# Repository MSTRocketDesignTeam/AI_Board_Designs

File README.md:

# AI_Board_Designs
This is the repo for all of the KiCad documentation for any AI Board changes.

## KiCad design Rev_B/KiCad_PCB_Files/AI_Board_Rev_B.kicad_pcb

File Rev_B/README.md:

This is the folder location for Rev_B of the AI Board designed by Isaac Lough for Missouri S&T Rocket Design Team.

The documentaiton for all of the reasoning is located here: https://mailmissouri.sharepoint.com/:w:/r/sites/RocketDesignTeam409-Ogrp/_layouts/15/Doc.aspx?sourcedoc=%7B42161E26-5CDD-4F6A-B8BB-66B7CA16C9B1%7D&file=AI%20Board%20Redesign%20-%20Unofficial%20Preliminary%20Research.docx&action=default&mobileredirect=true

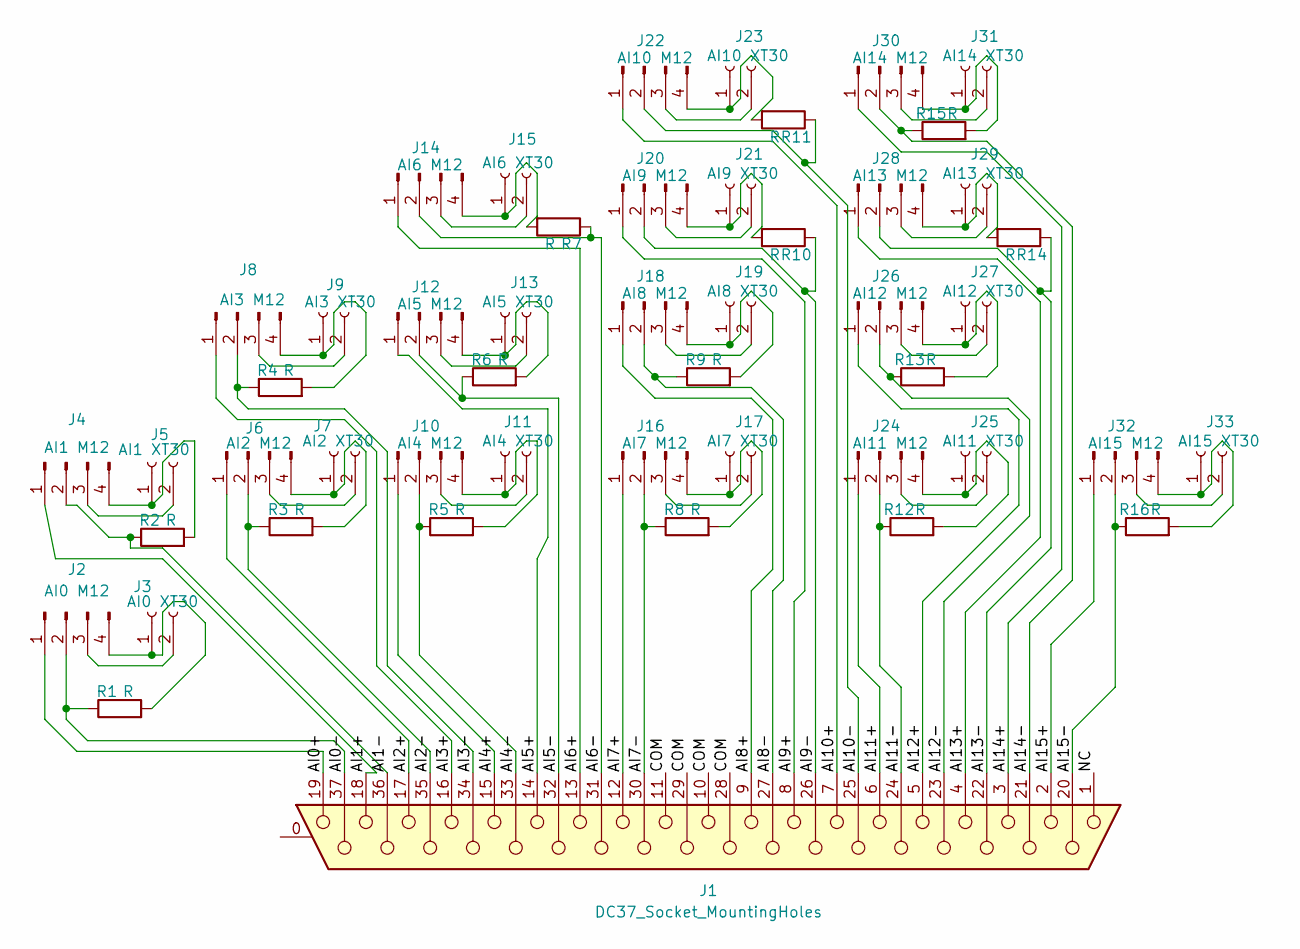
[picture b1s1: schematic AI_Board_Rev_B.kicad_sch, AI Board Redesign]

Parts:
J1: DC37_Socket_MountingHoles; DSUB-37_Socket_Vertical_P2.77x2.84mm_MountingHoles
J2: AI0 M12; M12 A-Code Amphenol
J3: AI0 XT30; AMASS_XT30U-F_1x02_P5.0mm_Vertical
J4: AI1 M12; M12 A-Code Amphenol
J5: AI1 XT30; AMASS_XT30U-F_1x02_P5.0mm_Vertical
J6: AI2 M12; M12 A-Code Amphenol
J7: AI2 XT30; AMASS_XT30U-F_1x02_P5.0mm_Vertical
J8: AI3 M12; M12 A-Code Amphenol
J9: AI3 XT30; AMASS_XT30U-F_1x02_P5.0mm_Vertical
J10: AI4 M12; M12 A-Code Amphenol
J11: AI4 XT30; AMASS_XT30U-F_1x02_P5.0mm_Vertical
J12: AI5 M12; M12 A-Code Amphenol
J13: AI5 XT30; AMASS_XT30U-F_1x02_P5.0mm_Vertical
J14: AI6 M12; M12 A-Code Amphenol
J15: AI6 XT30; AMASS_XT30U-F_1x02_P5.0mm_Vertical
J16: AI7 M12; M12 A-Code Amphenol
J17: AI7 XT30; AMASS_XT30U-F_1x02_P5.0mm_Vertical
J18: AI8 M12; M12 A-Code Amphenol
J19: AI8 XT30; AMASS_XT30U-F_1x02_P5.0mm_Vertical
J20: AI9 M12; M12 A-Code Amphenol
J21: AI9 XT30; AMASS_XT30U-F_1x02_P5.0mm_Vertical
J22: AI10 M12; M12 A-Code Amphenol
J23: AI10 XT30; AMASS_XT30U-F_1x02_P5.0mm_Vertical
J24: AI11 M12; M12 A-Code Amphenol
J25: AI11 XT30; AMASS_XT30U-F_1x02_P5.0mm_Vertical
J26: AI12 M12; M12 A-Code Amphenol
J27: AI12 XT30; AMASS_XT30U-F_1x02_P5.0mm_Vertical
J28: AI13 M12; M12 A-Code Amphenol
J29: AI13 XT30; AMASS_XT30U-F_1x02_P5.0mm_Vertical
J30: AI14 M12; M12 A-Code Amphenol
J31: AI14 XT30; AMASS_XT30U-F_1x02_P5.0mm_Vertical
J32: AI15 M12; M12 A-Code Amphenol
J33: AI15 XT30; AMASS_XT30U-F_1x02_P5.0mm_Vertical
R1, R2, R3, R4, R5, R6, R7, R8, R9, R10, R11, R12, R13, R14, R15, R16: R; R_Axial_DIN0207_L6.3mm_D2.5mm_P10.16mm_Horizontal

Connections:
/AI0+: J1.19, J2.1
/AI0-: J1.37, J2.2, R1.1
/AI1+: J1.18, J4.1
/AI1-: J1.36, J4.2, R2.1
/AI2+: J1.17, J6.1
/AI2-: J1.35, J6.2, R3.1
/AI3+: J1.16, J8.1
/AI3-: J1.34, J8.2, R4.1
/AI4+: J1.15, J10.1
/AI4-: J1.33, J10.2, R5.1
/AI5+: J1.14, J12.1
/AI5-: J1.32, J12.2, R6.1
/AI6+: J1.13, J14.1
/AI6-: J1.31, J14.2, R7.1
/AI7+: J1.12, J16.1
/AI7-: J1.30, J16.2, R8.1
/AI8+: J1.9, J18.1
/AI8-: J1.27, J18.2, R9.1
/AI9+: J1.8, J20.1
/AI9-: J1.26, J20.2, R10.1
/AI10+: J1.7, J22.1
/AI10-: J1.25, J22.2, R11.1
/AI11+: J1.6, J24.1
/AI11-: J1.24, J24.2, R12.1
/AI12+: J1.5, J26.1
/AI12-: J1.23, J26.2, R13.1
/AI13+: J1.4, J28.1
/AI13-: J1.22, J28.2, R14.1
/AI14+: J1.3, J30.1
/AI14-: J1.21, J30.2, R15.1
/AI15+: J1.2, J32.1
/AI15-: J1.20, J32.2, R16.1
/COM: J1.10, J1.11, J1.28, J1.29
/NC: J1.1
unnamed: J2.3, J3.2
unnamed: J2.4, J3.1, R1.2
unnamed: J4.3, J5.2
unnamed: J4.4, J5.1, R2.2
unnamed: J6.3, J7.2
unnamed: J6.4, J7.1, R3.2
unnamed: J8.3, J9.2
unnamed: J8.4, J9.1, R4.2
unnamed: J10.3, J11.2
unnamed: J10.4, J11.1, R5.2
unnamed: J12.3, J13.2
unnamed: J12.4, J13.1, R6.2
unnamed: J14.3, J15.2
unnamed: J14.4, J15.1, R7.2
unnamed: J16.3, J17.2
unnamed: J16.4, J17.1, R8.2
unnamed: J18.3, J19.2
unnamed: J18.4, J19.1, R9.2
unnamed: J20.3, J21.2
unnamed: J20.4, J21.1, R10.2
unnamed: J22.3, J23.2
unnamed: J22.4, J23.1, R11.2
unnamed: J24.3, J25.2
unnamed: J24.4, J25.1, R12.2
unnamed: J26.3, J27.2
unnamed: J26.4, J27.1, R13.2
unnamed: J28.3, J29.2
unnamed: J28.4, J29.1, R14.2
unnamed: J30.3, J31.2
unnamed: J30.4, J31.1, R15.2
unnamed: J32.3, J33.2
unnamed: J32.4, J33.1, R16.2

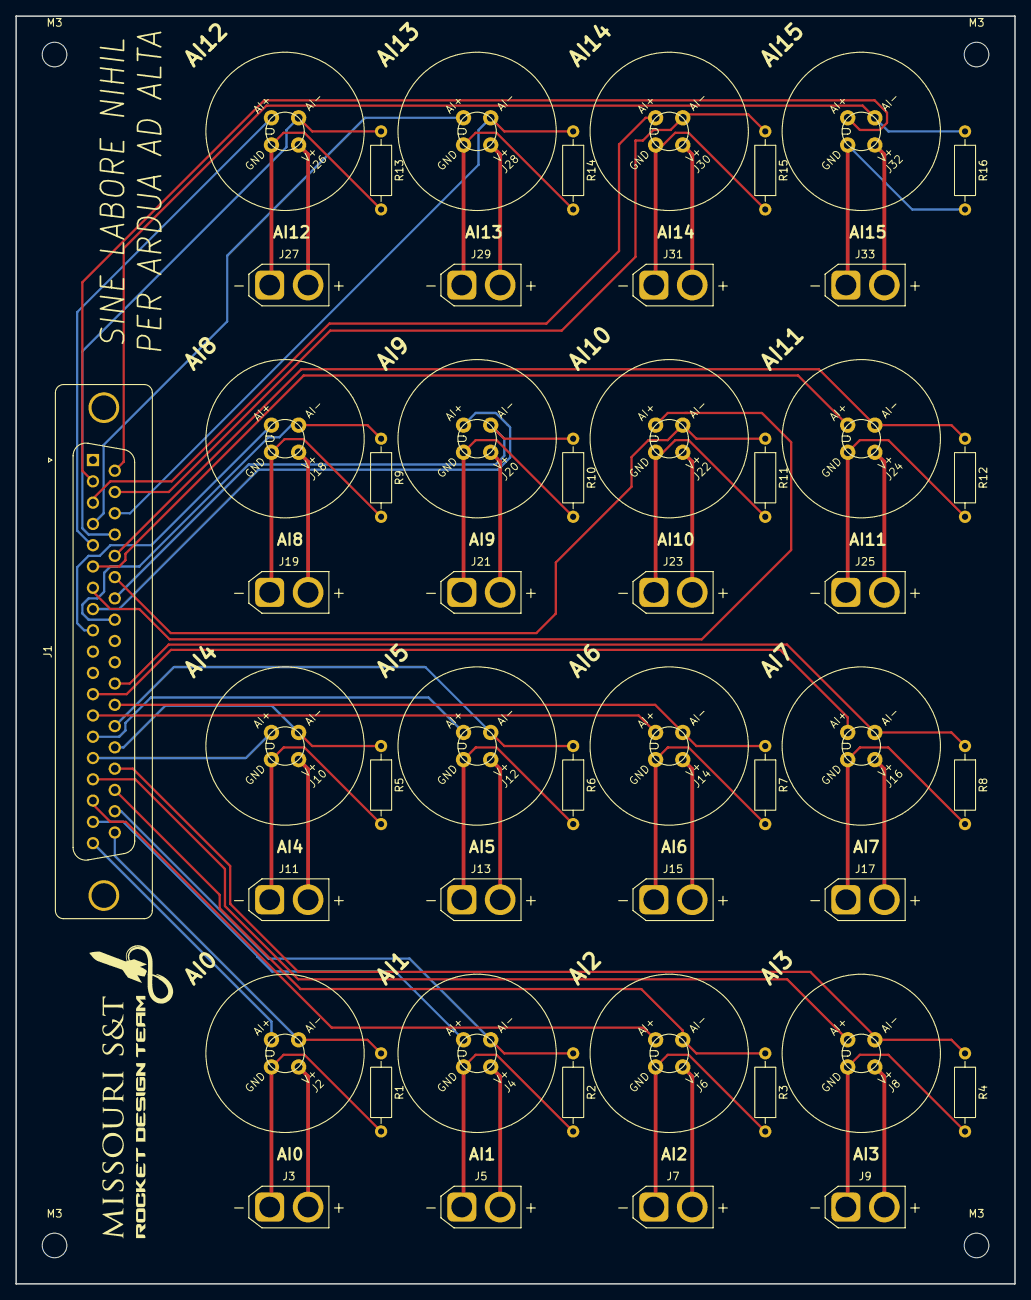
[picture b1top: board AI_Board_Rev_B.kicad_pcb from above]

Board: 2 copper layers, 130.0 x 165.0 mm, 53 parts (0 on the bottom side), 65 nets.

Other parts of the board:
M3, M3#2, M3#3, M3#4: MountingHole_3.2mm_M3

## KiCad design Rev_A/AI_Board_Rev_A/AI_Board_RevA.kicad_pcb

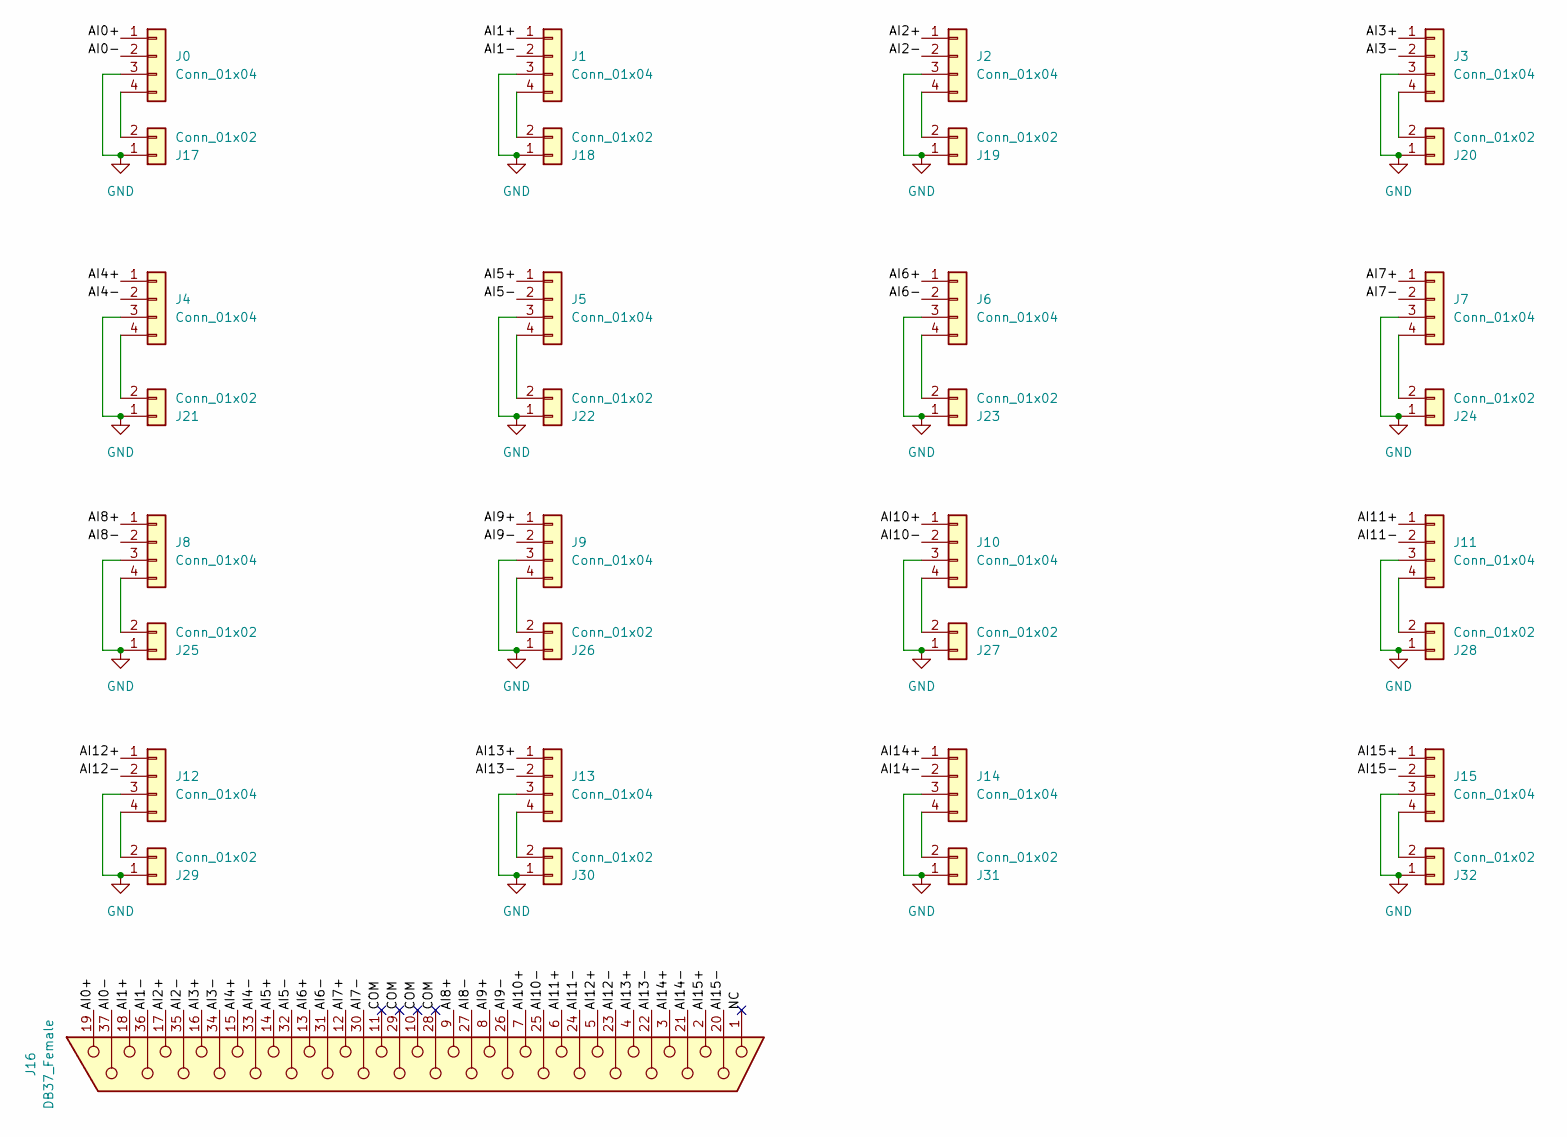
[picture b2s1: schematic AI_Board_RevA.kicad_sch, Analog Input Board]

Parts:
J0, J1, J2, J3, J4, J5, J6, J7, J8, J9, J10, J11, J12, J13, J14, J15: Conn_01x04; TENSILITY_54-00278
J16: DB37_Female; DSUB-37_Female_Vertical_P2.77x2.84mm_MountingHoles
J17, J18, J19, J20, J21, J22, J23, J24, J25, J26, J27, J28, J29, J30, J31, J32: Conn_01x02; AMASS_XT30UPB-F_1x02_P5.0mm_Vertical

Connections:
/AI0+: J0.1, J16.19
/AI0-: J0.2, J16.37
/AI1+: J1.1, J16.18
/AI1-: J1.2, J16.36
/AI2+: J2.1, J16.17
/AI2-: J2.2, J16.35
/AI3+: J3.1, J16.16
/AI3-: J3.2, J16.34
/AI4+: J4.1, J16.15
/AI4-: J4.2, J16.33
/AI5+: J5.1, J16.14
/AI5-: J5.2, J16.32
/AI6+: J6.1, J16.13
/AI6-: J6.2, J16.31
/AI7+: J7.1, J16.12
/AI7-: J7.2, J16.30
/AI8+: J8.1, J16.9
/AI8-: J8.2, J16.27
/AI9+: J9.1, J16.8
/AI9-: J9.2, J16.26
/AI10+: J10.1, J16.7
/AI10-: J10.2, J16.25
/AI11+: J11.1, J16.6
/AI11-: J11.2, J16.24
/AI12+: J12.1, J16.5
/AI12-: J12.2, J16.23
/AI13+: J13.1, J16.4
/AI13-: J13.2, J16.22
/AI14+: J14.1, J16.3
/AI14-: J14.2, J16.21
/AI15+: J15.1, J16.2
/AI15-: J15.2, J16.20
/COM: J16.10, J16.11, J16.28, J16.29
/NC: J16.1
GND: J0.3, J1.3, J2.3, J3.3, J4.3, J5.3, J6.3, J7.3, J8.3, J9.3, J10.3, J11.3, J12.3, J13.3, J14.3, J15.3, J17.1, J18.1, J19.1, J20.1, J21.1, J22.1, J23.1, J24.1, J25.1, J26.1, J27.1, J28.1, J29.1, J30.1, J31.1, J32.1
unnamed: J0.4, J17.2
unnamed: J1.4, J18.2
unnamed: J10.4, J27.2
unnamed: J11.4, J28.2
unnamed: J12.4, J29.2
unnamed: J13.4, J30.2
unnamed: J14.4, J31.2
unnamed: J15.4, J32.2
unnamed: J2.4, J19.2
unnamed: J3.4, J20.2
unnamed: J4.4, J21.2
unnamed: J5.4, J22.2
unnamed: J6.4, J23.2
unnamed: J7.4, J24.2
unnamed: J8.4, J25.2
unnamed: J9.4, J26.2

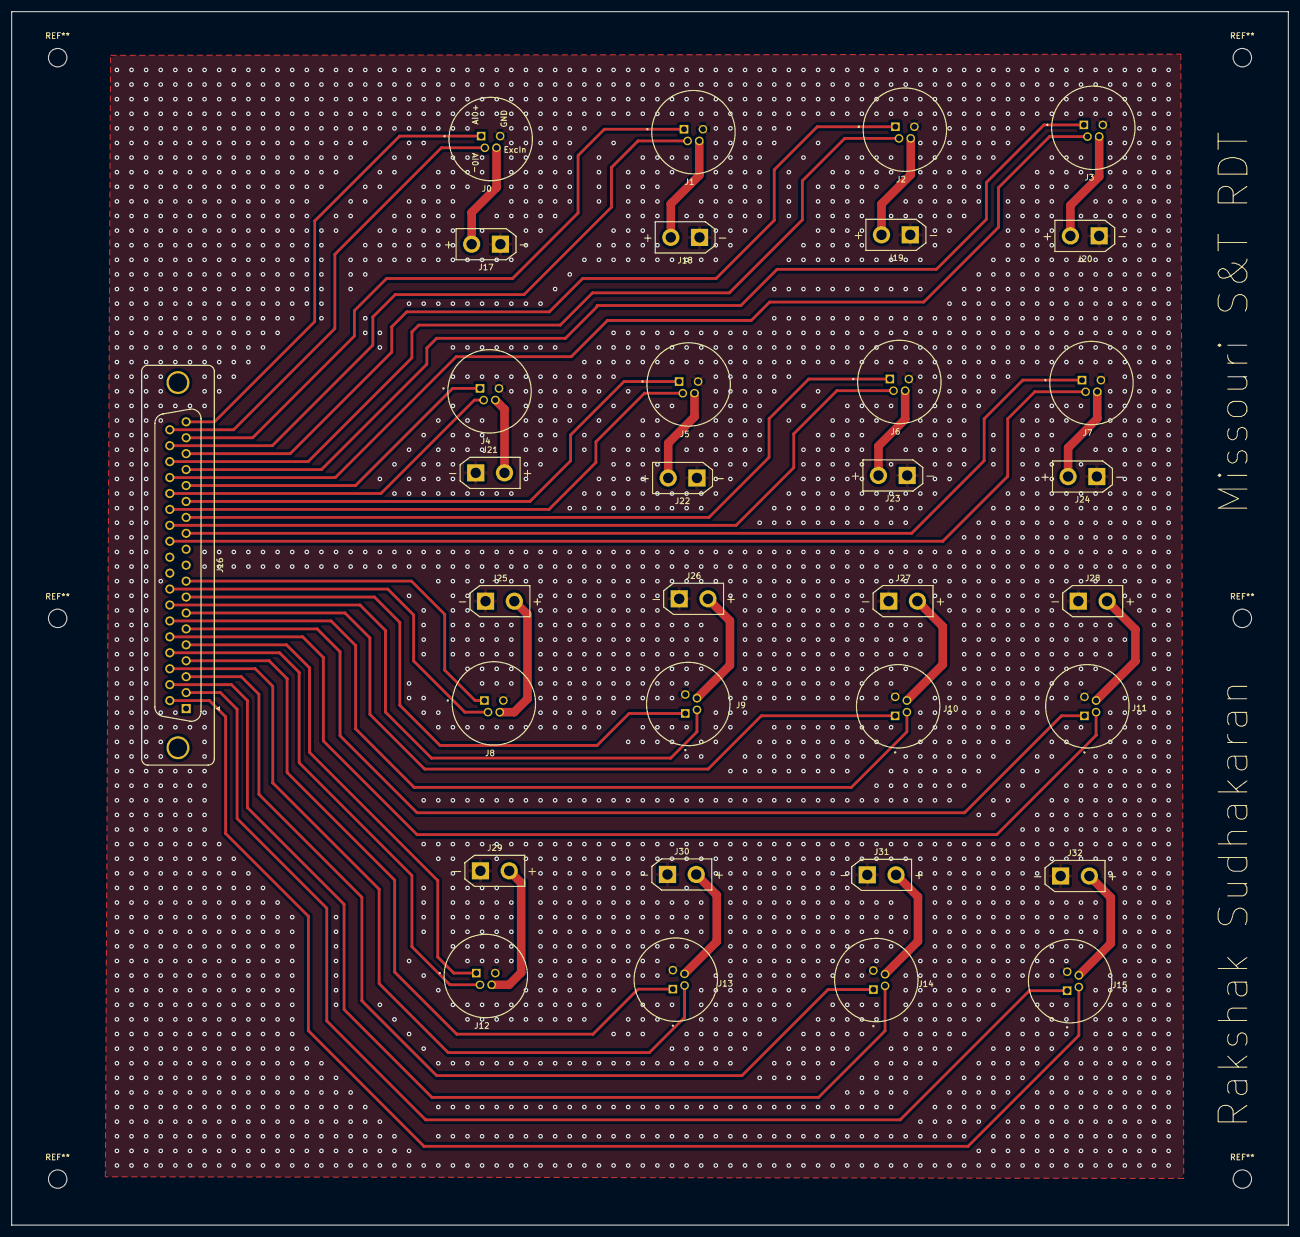
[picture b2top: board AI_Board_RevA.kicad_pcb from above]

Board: 2 copper layers, 222.0 x 211.0 mm, 33 parts (0 on the bottom side), 50 nets.

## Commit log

2025-07-13 Create KiCad Files
2025-07-13 Create placeholder
2025-07-15 Rename KiCad Files/KiCad Libraries/Connector_AMASS.pretty/AMASS_MR30PW-FB_1x03_P3.50mm_Horizontal.kicad_mod to Rev_B/KiCad_Libraries/AMASS_MR30PW-FB_1x03_P3.50mm_Horizontal.kicad_mod
